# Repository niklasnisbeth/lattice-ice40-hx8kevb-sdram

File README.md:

August, 2016, designed in Labitat in Copenhagen.

Schematic and layout for board with SDRAM and SD card reader that plugs in to the Lattice HX8K Breakout Board and remaing GPIO routed to a header.

The RAM Tested and working with a modified version of Lattice's example SDRAM controller[0], with memtest running from an STM32F4 expansion board that also plugs into the HX8K Breakout. The SD card reader has not been tested.

HOWEVER, for rev. A (see git history): Some of the pins on the HX8K expansion headers are also used for other functions. Particular, as routed D0 is also connected to the FTDI chip. Fortunately, GPIO6 is right next to it, so you can just cut off pin 12 on the header, and bridge pin 10 and 12. This has been fixed in the new version.

For FPGA code, see https://github.com/knielsen/ice40-stm32-sdram, which uses the STM32 expansion board we also made.

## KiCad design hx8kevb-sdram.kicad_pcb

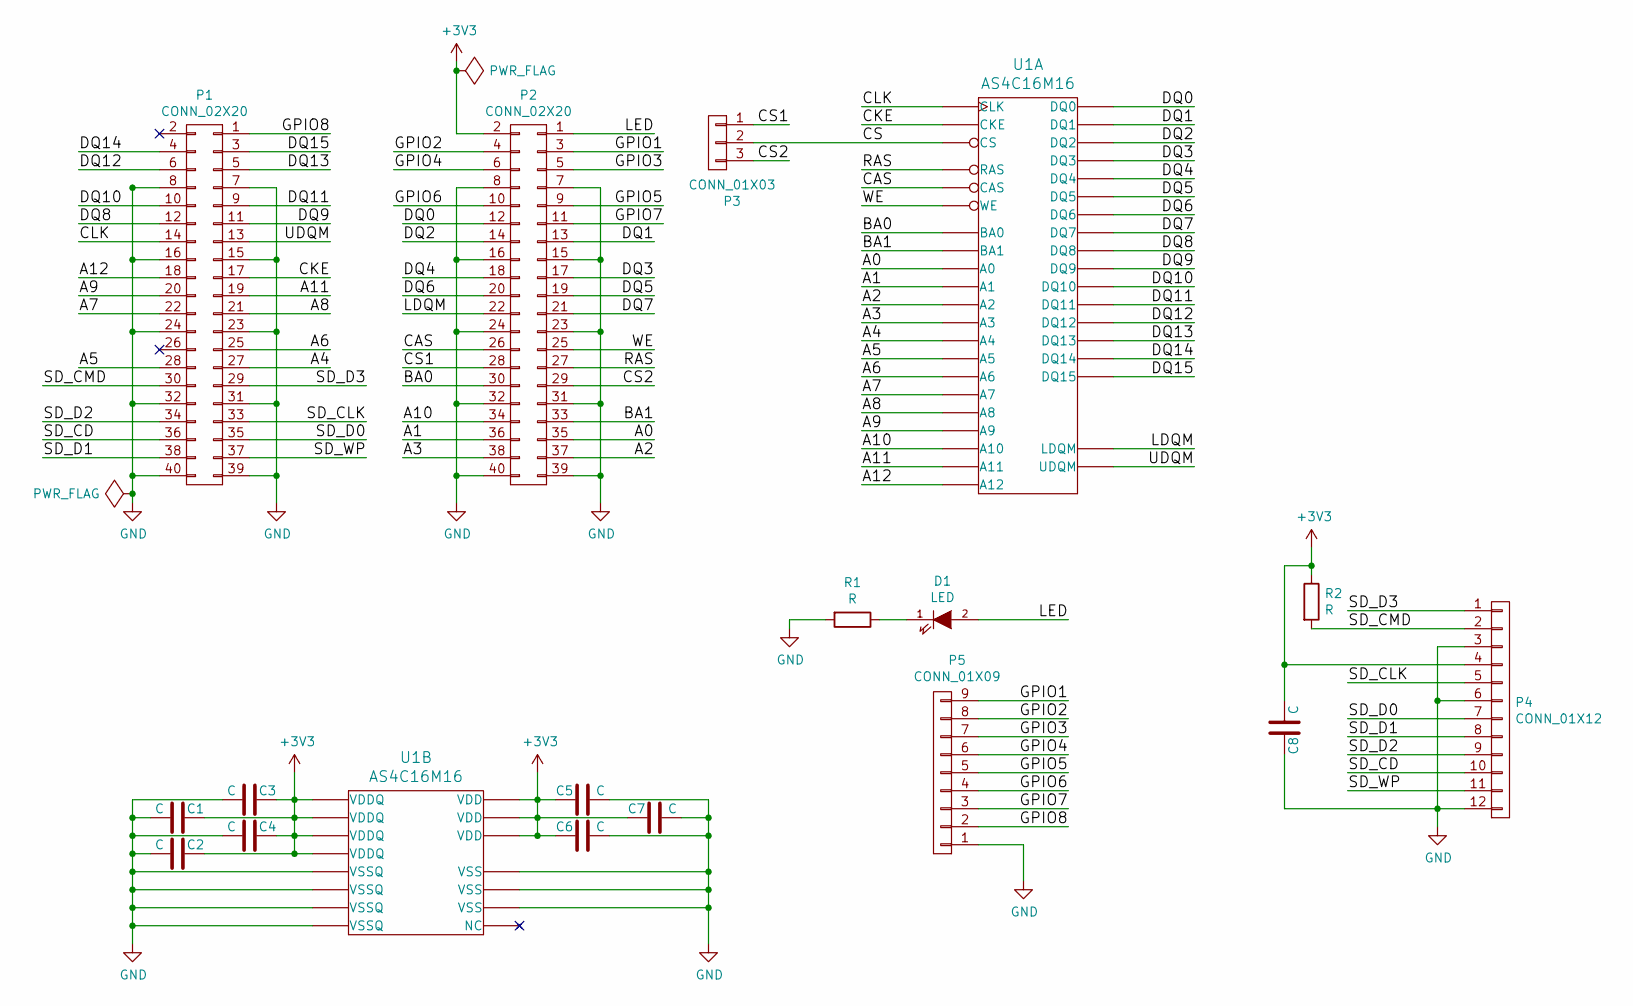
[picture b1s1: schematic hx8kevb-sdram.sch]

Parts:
C1, C2, C3, C4, C5, C6, C7, C8: C; C_0805_HandSoldering
D1: LED; LED_0805
P1, P2: CONN_02X20; Pin_Header_Straight_2x20
P3: CONN_01X03; Pin_Header_Straight_1x03
P4: CONN_01X12; SD_CARD_10100
P5: CONN_01X09; Pin_Header_Straight_1x09
R1, R2: R; R_0805_HandSoldering
U1: AS4C16M16; TSOP-54

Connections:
+3V3: C1.1, C2.1, C3.1, C4.1, C5.2, C6.2, C7.2, C8.1, P2.2, P4.4, R2.1, U1.1 (VDD), U1.3 (VDDQ), U1.9 (VDDQ), U1.14 (VDD), U1.27 (VDD), U1.43 (VDDQ), U1.49 (VDDQ)
/A0: P2.35, U1.23 (A0)
/A1: P2.36, U1.24 (A1)
/A2: P2.37, U1.25 (A2)
/A3: P2.38, U1.26 (A3)
/A4: P1.27, U1.29 (A4)
/A5: P1.28, U1.30 (A5)
/A6: P1.25, U1.31 (A6)
/A7: P1.22, U1.32 (A7)
/A8: P1.21, U1.33 (A8)
/A9: P1.20, U1.34 (A9)
/A10: P2.34, U1.22 (A10)
/A11: P1.19, U1.35 (A11)
/A12: P1.18, U1.36 (A12)
/BA0: P2.30, U1.20 (BA0)
/BA1: P2.33, U1.21 (BA1)
/CAS: P2.26, U1.17 (CAS)
/CKE: P1.17, U1.37 (CKE)
/CLK: P1.14, U1.38 (CLK)
/CS: P3.2, U1.19 (CS)
/CS1: P2.28, P3.1
/CS2: P2.29, P3.3
/DQ0: P2.12, U1.2 (DQ0)
/DQ1: P2.13, U1.4 (DQ1)
/DQ2: P2.14, U1.5 (DQ2)
/DQ3: P2.17, U1.7 (DQ3)
/DQ4: P2.18, U1.8 (DQ4)
/DQ5: P2.19, U1.10 (DQ5)
/DQ6: P2.20, U1.11 (DQ6)
/DQ7: P2.21, U1.13 (DQ7)
/DQ8: P1.12, U1.42 (DQ8)
/DQ9: P1.11, U1.44 (DQ9)
/DQ10: P1.10, U1.45 (DQ10)
/DQ11: P1.9, U1.47 (DQ11)
/DQ12: P1.6, U1.48 (DQ12)
/DQ13: P1.5, U1.50 (DQ13)
/DQ14: P1.4, U1.51 (DQ14)
/DQ15: P1.3, U1.53 (DQ15)
/GPIO1: P2.3, P5.9
/GPIO2: P2.4, P5.8
/GPIO3: P2.5, P5.7
/GPIO4: P2.6, P5.6
/GPIO5: P2.9, P5.5
/GPIO6: P2.10, P5.4
/GPIO7: P2.11, P5.3
/GPIO8: P1.1, P5.2
/LDQM: P2.22, U1.15 (LDQM)
/LED: D1.2 (A), P2.1
/RAS: P2.27, U1.18 (RAS)
/SD_CD: P1.36, P4.10
/SD_CLK: P1.33, P4.5
/SD_CMD: P1.30, P4.2, R2.2
/SD_D0: P1.35, P4.7
/SD_D1: P1.38, P4.8
/SD_D2: P1.34, P4.9
/SD_D3: P1.29, P4.1
/SD_WP: P1.37, P4.11
/UDQM: P1.13, U1.39 (UDQM)
/WE: P2.25, U1.16 (WE)
GND: C1.2, C2.2, C3.2, C4.2, C5.1, C6.1, C7.1, C8.2, P1.7, P1.8, P1.15, P1.16, P1.23, P1.24, P1.31, P1.32, P1.39, P1.40, P2.7, P2.8, P2.15, P2.16, P2.23, P2.24, P2.31, P2.32, P2.39, P2.40, P4.3, P4.6, P4.12, P5.1, R1.2, U1.6 (VSSQ), U1.12 (VSSQ), U1.28 (VSS), U1.41 (VSS), U1.46 (VSSQ), U1.52 (VSSQ), U1.54 (VSS)
unnamed: D1.1 (K), R1.1

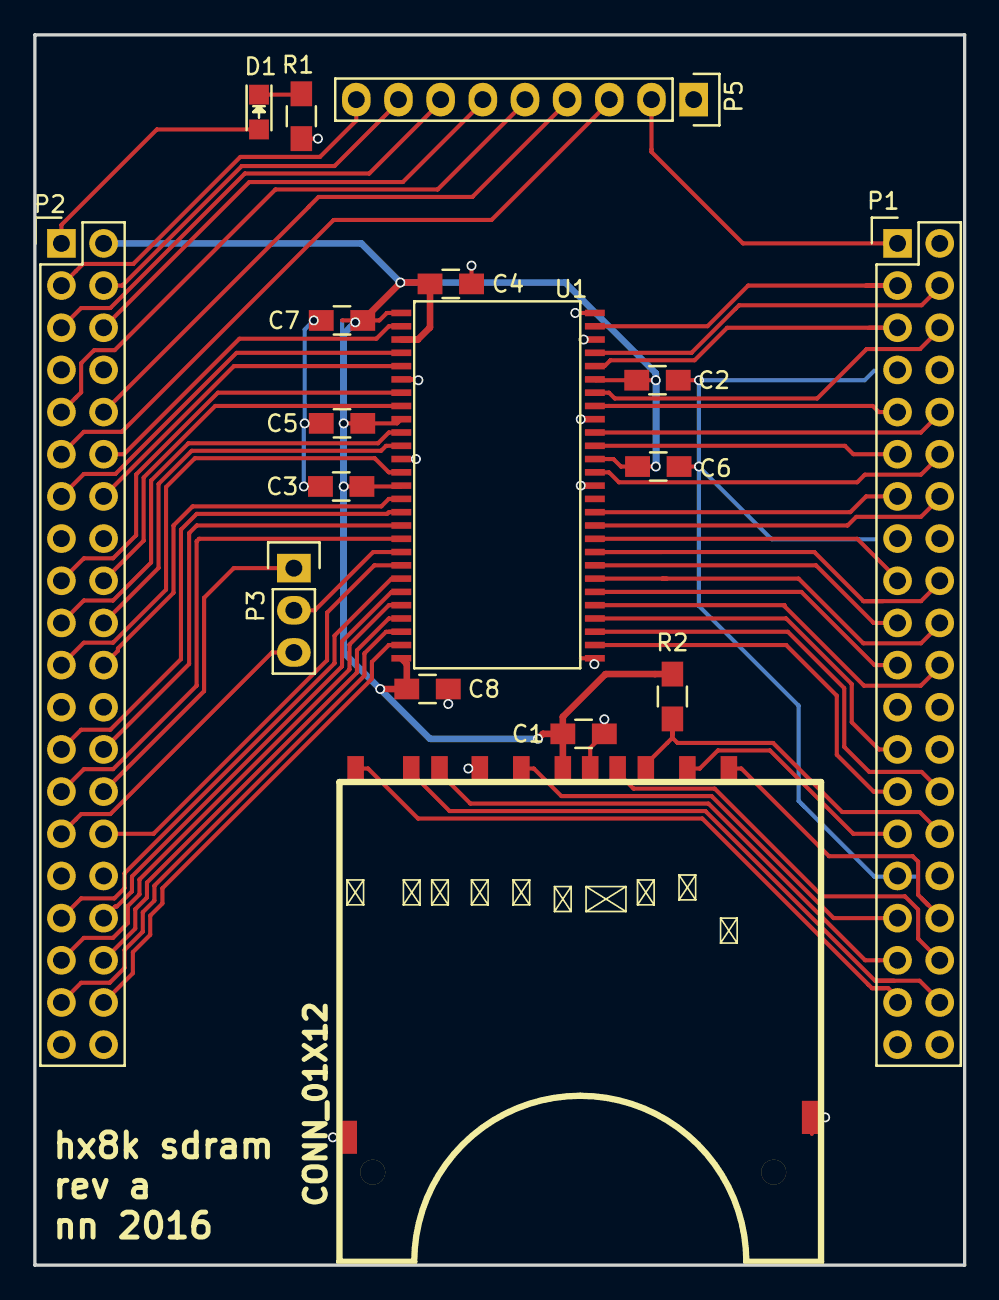
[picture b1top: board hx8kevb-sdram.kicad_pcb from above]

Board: 2 copper layers, 56.0 x 74.1 mm, 17 parts (0 on the bottom side), 61 nets.

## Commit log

2016-08-05 init
2016-12-20 rev b
